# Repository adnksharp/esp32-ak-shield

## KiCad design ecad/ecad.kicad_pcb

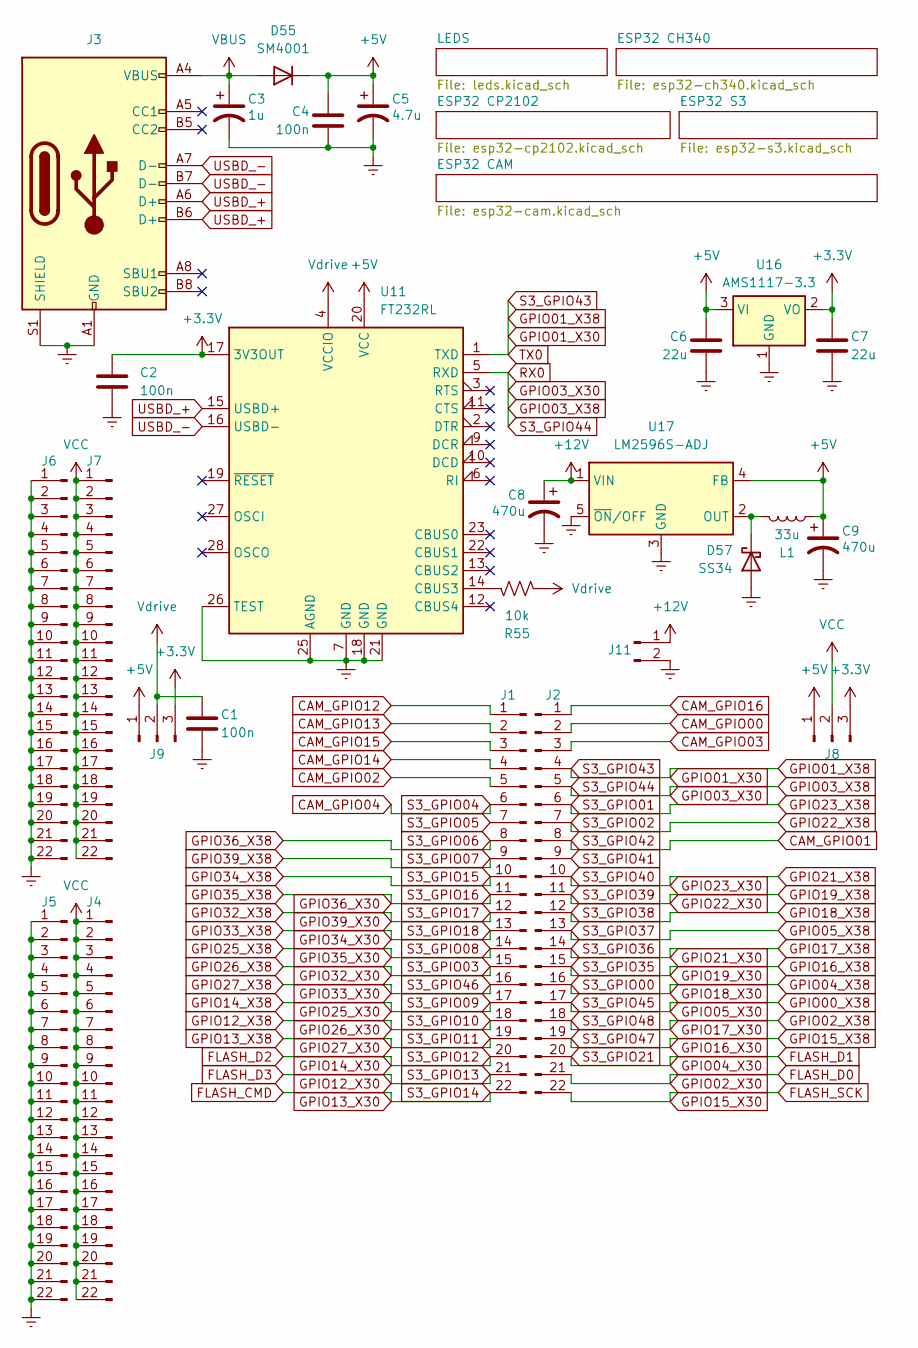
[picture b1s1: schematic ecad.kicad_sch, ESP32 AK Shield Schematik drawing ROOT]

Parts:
C1, C2, C4: 100n; C_0805_2012Metric_Pad1.18x1.45mm_HandSolder
C3: 1u; CP_Elec_4x5.4
C5: 4.7u; CP_Elec_4x5.4
C6, C7: 22u; C_0805_2012Metric_Pad1.18x1.45mm_HandSolder
C8, C9: 470u; CP_Elec_8x10.5
D55: SM4001; D_MELF
D57: SS34; D_SMA
J1, J2, J4, J5, J6, J7: Conn_01x22_Pin; PinHeader_1x22_P2.54mm_Vertical
J3: USB_C; USB_C_Receptacle_Palconn_UTC16-G
J8, J9: Conn_01x03_Pin; PinHeader_1x03_P2.54mm_Vertical
J11: Conn_01x02_Pin; BarrelJack_GCT_DCJ200-10-A_Horizontal
L1: 33u; L_6.3x6.3_H3
R55: 10k; R_0805_2012Metric_Pad1.20x1.40mm_HandSolder
U11: FT232RL; SSOP-28_5.3x10.2mm_P0.65mm
U16: AMS1117-3.3; SOT-223-3_TabPin2
U17: LM2596S-ADJ; TO-263-5_TabPin3

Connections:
+3.3V: C2.1, C7.1, J8.3, J9.3, U11.17 (3V3OUT), U16.2 (VO); also elsewhere on the board
+5V: C4.1, C5.1, C6.1, C9.1, D55.1 (K), J8.1, J9.1, L1.2, U11.20 (VCC), U16.3 (VI), U17.4 (FB); also elsewhere on the board
+12V: C8.1, J11.1, U17.1 (VIN); also elsewhere on the board
CAM_GPIO00: J2.2; also elsewhere on the board
CAM_GPIO01: J2.8; also elsewhere on the board
CAM_GPIO02: J1.5; also elsewhere on the board
CAM_GPIO03: J2.3; also elsewhere on the board
CAM_GPIO04: J1.6; also elsewhere on the board
CAM_GPIO12: J1.1; also elsewhere on the board
CAM_GPIO13: J1.2; also elsewhere on the board
CAM_GPIO14: J1.4; also elsewhere on the board
CAM_GPIO15: J1.3; also elsewhere on the board
CAM_GPIO16: J2.1; also elsewhere on the board
Earth: C1.2, C2.2, C3.2, C4.2, C5.2, C6.2, C7.2, C8.2, C9.2, D57.2 (A), J3.A1 (GND), J3.A12 (GND), J3.B1 (GND), J3.B12 (GND), J3.S1 (SHIELD), J5.1, J5.2, J5.3, J5.4, J5.5, J5.6, J5.7, J5.8, J5.9, J5.10, J5.11, J5.12, J5.13, J5.14, J5.15, J5.16, J5.17, J5.18, J5.19, J5.20, J5.21, J5.22, J6.1, J6.2, J6.3, J6.4, J6.5, J6.6, J6.7, J6.8, J6.9, J6.10, J6.11, J6.12, J6.13, J6.14, J6.15, J6.16, J6.17, J6.18, J6.19, J6.20, J6.21, J6.22, J11.2, U11.7 (GND), U11.18 (GND), U11.21 (GND), U11.25 (AGND), U11.26 (TEST), U16.1 (GND), U17.3 (GND), U17.5 (~ON/OFF); also elsewhere on the board
FLASH_CMD: J1.22; also elsewhere on the board
FLASH_D0: J2.21; also elsewhere on the board
FLASH_D1: J2.20; also elsewhere on the board
FLASH_D2: J1.20; also elsewhere on the board
FLASH_D3: J1.21; also elsewhere on the board
FLASH_SCK: J2.22; also elsewhere on the board
GPIO00_X38: J2.17; also elsewhere on the board
GPIO01_X30: J2.4, U11.1 (TXD); also elsewhere on the board
GPIO02_X38: J2.18; also elsewhere on the board
GPIO03_X30: J2.5, U11.5 (RXD); also elsewhere on the board
GPIO04_X38: J2.16; also elsewhere on the board
GPIO05_X38: J2.13; also elsewhere on the board
GPIO12_X38: J1.18; also elsewhere on the board
GPIO13_X38: J1.19; also elsewhere on the board
GPIO14_X38: J1.17; also elsewhere on the board
GPIO15_X38: J2.19; also elsewhere on the board
GPIO16_X38: J2.15; also elsewhere on the board
GPIO17_X38: J2.14; also elsewhere on the board
GPIO18_X38: J2.12; also elsewhere on the board
GPIO19_X38: J2.11; also elsewhere on the board
GPIO21_X38: J2.10; also elsewhere on the board
GPIO22_X38: J2.7; also elsewhere on the board
GPIO23_X38: J2.6; also elsewhere on the board
GPIO25_X38: J1.14; also elsewhere on the board
GPIO26_X38: J1.15; also elsewhere on the board
GPIO27_X38: J1.16; also elsewhere on the board
GPIO32_X38: J1.12; also elsewhere on the board
GPIO33_X38: J1.13; also elsewhere on the board
GPIO34_X38: J1.10; also elsewhere on the board
GPIO35_X38: J1.11; also elsewhere on the board
GPIO36_X38: J1.8; also elsewhere on the board
GPIO39_X38: J1.9; also elsewhere on the board
unnamed: D57.1 (K), L1.1, U17.2 (OUT)
unnamed: R55.1, U11.14 (CBUS3)
S3_GPIO05: J1.7; also elsewhere on the board
S3_GPIO41: J2.9; also elsewhere on the board
USBD_+: J3.A6 (D+), J3.B6 (D+), U11.15 (USBD+)
USBD_-: J3.A7 (D-), J3.B7 (D-), U11.16 (USBD-)
VBUS: C3.1, D55.2 (A), J3.A4 (VBUS), J3.A9 (VBUS), J3.B4 (VBUS), J3.B9 (VBUS); also elsewhere on the board
VCC: J4.1, J4.2, J4.3, J4.4, J4.5, J4.6, J4.7, J4.8, J4.9, J4.10, J4.11, J4.12, J4.13, J4.14, J4.15, J4.16, J4.17, J4.18, J4.19, J4.20, J4.21, J4.22, J7.1, J7.2, J7.3, J7.4, J7.5, J7.6, J7.7, J7.8, J7.9, J7.10, J7.11, J7.12, J7.13, J7.14, J7.15, J7.16, J7.17, J7.18, J7.19, J7.20, J7.21, J7.22, J8.2
Vdrive: C1.1, J9.2, R55.2, U11.4 (VCCIO)

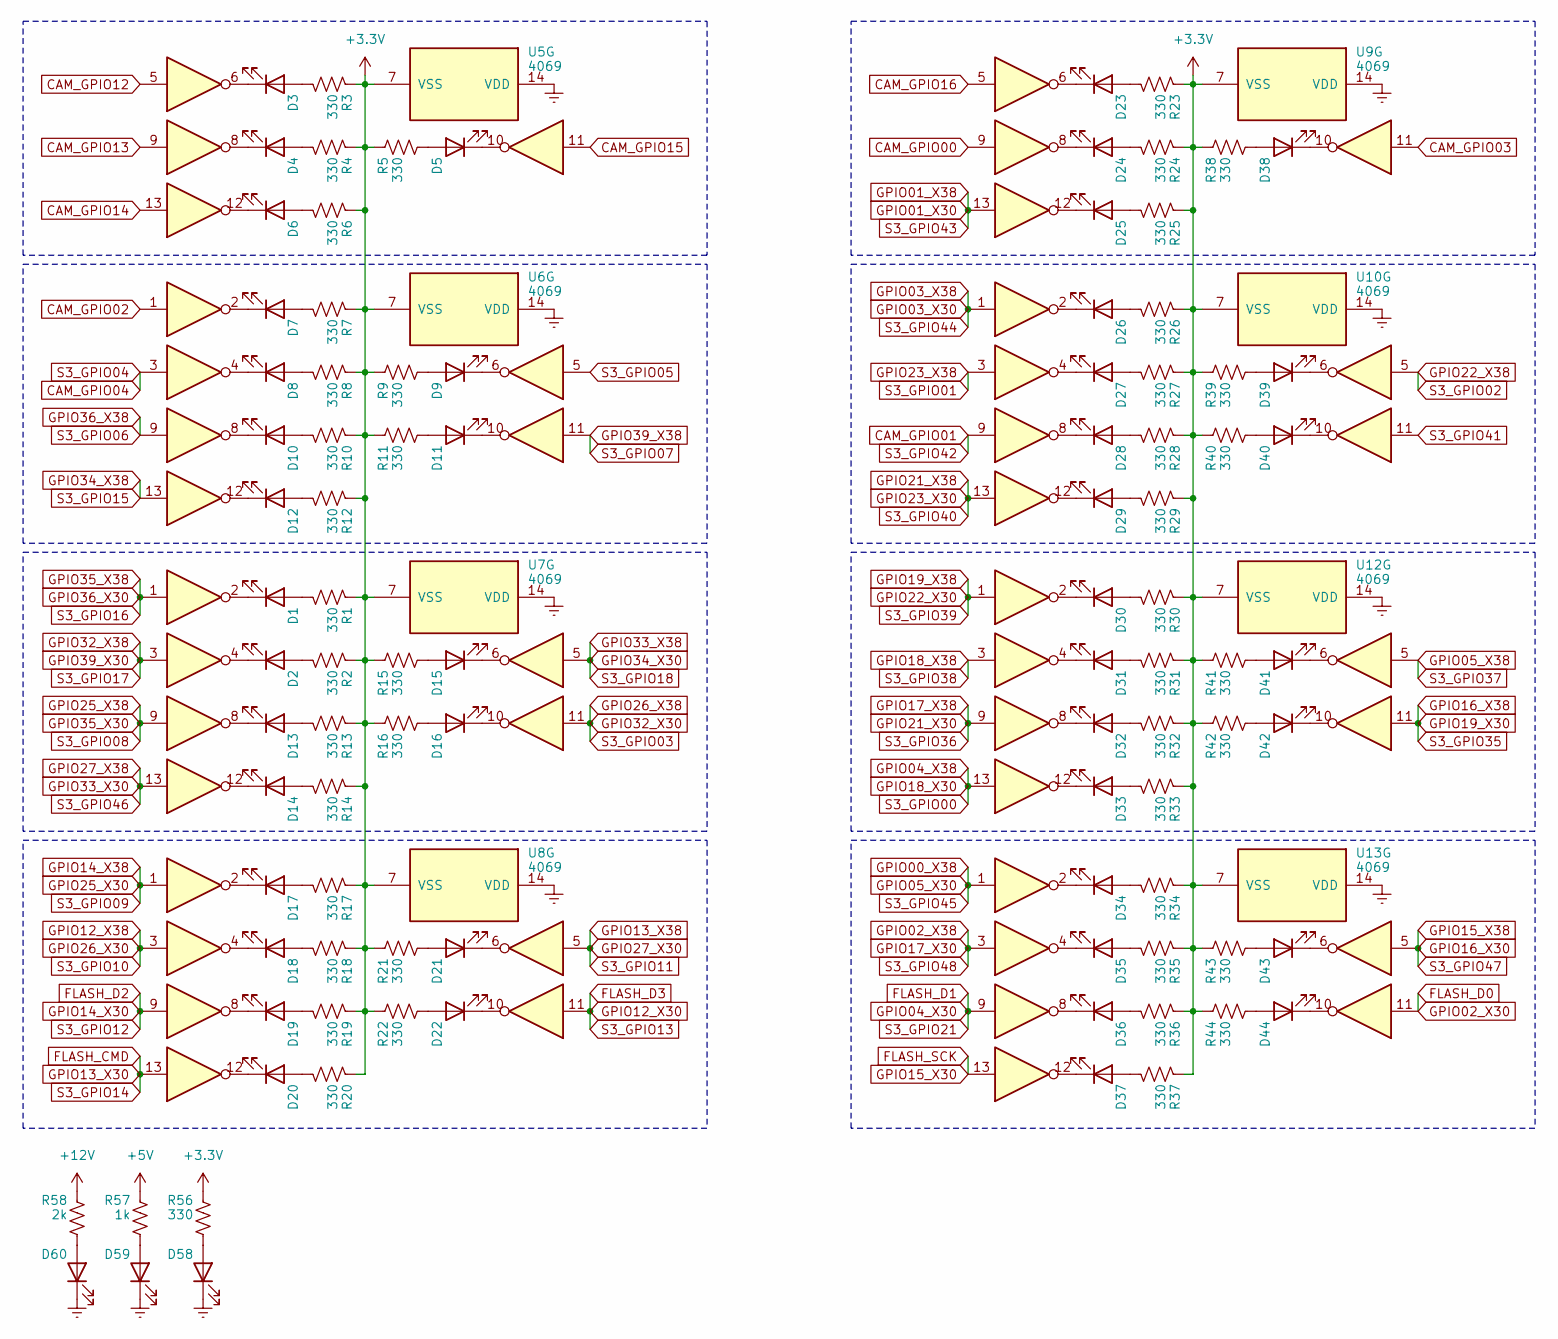
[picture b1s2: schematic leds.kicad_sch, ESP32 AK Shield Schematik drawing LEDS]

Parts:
D1, D2, D3, D4, D5, D6, D7, D8, D9, D10, D11, D12, D13, D14, D15, D16, D17, D18, D19, D20, D21, D22, D23, D24, D25, D26, D27, D28, D29, D30, D31, D32, D33, D34, D35, D36, D37, D38, D39, D40, D41, D42, D43, D44, D58, D59, D60: LED; LED_0805_2012Metric_Pad1.15x1.40mm_HandSolder
R1, R2, R3, R4, R5, R6, R7, R8, R9, R10, R11, R12, R13, R14, R15, R16, R17, R18, R19, R20, R21, R22, R23, R24, R25, R26, R27, R28, R29, R30, R31, R32, R33, R34, R35, R36, R37, R38, R39, R40, R41, R42, R43, R44, R56: 330; R_0805_2012Metric_Pad1.20x1.40mm_HandSolder
R57: 1k; R_0805_2012Metric_Pad1.20x1.40mm_HandSolder
R58: 2k; R_0805_2012Metric_Pad1.20x1.40mm_HandSolder
U5, U6, U7, U8, U9, U10, U12, U13: 4069; DIP-14_W8.89mm_SMDSocket_LongPads

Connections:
+3.3V: R1.2, R2.2, R3.2, R4.2, R5.2, R6.2, R7.2, R8.2, R9.2, R10.2, R11.2, R12.2, R13.2, R14.2, R15.2, R16.2, R17.2, R18.2, R19.2, R20.2, R21.2, R22.2, R23.2, R24.2, R25.2, R26.2, R27.2, R28.2, R29.2, R30.2, R31.2, R32.2, R33.2, R34.2, R35.2, R36.2, R37.2, R38.2, R39.2, R40.2, R41.2, R42.2, R43.2, R44.2, R56.2, U5.7 (VSS), U6.7 (VSS), U7.7 (VSS), U8.7 (VSS), U9.7 (VSS), U10.7 (VSS), U12.7 (VSS), U13.7 (VSS); also elsewhere on the board
+5V: R57.2; also elsewhere on the board
+12V: R58.2; also elsewhere on the board
CAM_GPIO00: U9.9; also elsewhere on the board
CAM_GPIO01: U10.9; also elsewhere on the board
CAM_GPIO02: U6.1; also elsewhere on the board
CAM_GPIO03: U9.11; also elsewhere on the board
CAM_GPIO04: U6.3; also elsewhere on the board
CAM_GPIO12: U5.5; also elsewhere on the board
CAM_GPIO13: U5.9; also elsewhere on the board
CAM_GPIO14: U5.13; also elsewhere on the board
CAM_GPIO15: U5.11; also elsewhere on the board
CAM_GPIO16: U9.5; also elsewhere on the board
Earth: D58.1 (K), D59.1 (K), D60.1 (K), U5.14 (VDD), U6.14 (VDD), U7.14 (VDD), U8.14 (VDD), U9.14 (VDD), U10.14 (VDD), U12.14 (VDD), U13.14 (VDD); also elsewhere on the board
FLASH_CMD: U8.13; also elsewhere on the board
FLASH_D0: U13.11; also elsewhere on the board
FLASH_D1: U13.9; also elsewhere on the board
FLASH_D2: U8.9; also elsewhere on the board
FLASH_D3: U8.11; also elsewhere on the board
FLASH_SCK: U13.13; also elsewhere on the board
GPIO00_X38: U13.1; also elsewhere on the board
GPIO01_X30: U9.13; also elsewhere on the board
GPIO02_X38: U13.3; also elsewhere on the board
GPIO03_X30: U10.1; also elsewhere on the board
GPIO04_X38: U12.13; also elsewhere on the board
GPIO05_X38: U12.5; also elsewhere on the board
GPIO12_X38: U8.3; also elsewhere on the board
GPIO13_X38: U8.5; also elsewhere on the board
GPIO14_X38: U8.1; also elsewhere on the board
GPIO15_X38: U13.5; also elsewhere on the board
GPIO16_X38: U12.11; also elsewhere on the board
GPIO17_X38: U12.9; also elsewhere on the board
GPIO18_X38: U12.3; also elsewhere on the board
GPIO19_X38: U12.1; also elsewhere on the board
GPIO21_X38: U10.13; also elsewhere on the board
GPIO22_X38: U10.5; also elsewhere on the board
GPIO23_X38: U10.3; also elsewhere on the board
GPIO25_X38: U7.9; also elsewhere on the board
GPIO26_X38: U7.11; also elsewhere on the board
GPIO27_X38: U7.13; also elsewhere on the board
GPIO32_X38: U7.3; also elsewhere on the board
GPIO33_X38: U7.5; also elsewhere on the board
GPIO34_X38: U6.13; also elsewhere on the board
GPIO35_X38: U7.1; also elsewhere on the board
GPIO36_X38: U6.9; also elsewhere on the board
GPIO39_X38: U6.11; also elsewhere on the board
unnamed: D1.2 (A), R1.1
unnamed: D1.1 (K), U7.2
unnamed: D2.2 (A), R2.1
unnamed: D2.1 (K), U7.4
unnamed: D3.2 (A), R3.1
unnamed: D3.1 (K), U5.6
unnamed: D4.2 (A), R4.1
unnamed: D4.1 (K), U5.8
unnamed: D5.2 (A), R5.1
unnamed: D5.1 (K), U5.10
unnamed: D6.2 (A), R6.1
unnamed: D6.1 (K), U5.12
unnamed: D7.2 (A), R7.1
unnamed: D7.1 (K), U6.2
unnamed: D8.2 (A), R8.1
unnamed: D8.1 (K), U6.4
unnamed: D9.2 (A), R9.1
unnamed: D9.1 (K), U6.6
unnamed: D10.2 (A), R10.1
unnamed: D10.1 (K), U6.8
unnamed: D11.2 (A), R11.1
unnamed: D11.1 (K), U6.10
unnamed: D12.2 (A), R12.1
unnamed: D12.1 (K), U6.12
unnamed: D13.2 (A), R13.1
unnamed: D13.1 (K), U7.8
unnamed: D14.2 (A), R14.1
unnamed: D14.1 (K), U7.12
unnamed: D15.2 (A), R15.1
unnamed: D15.1 (K), U7.6
unnamed: D16.2 (A), R16.1
unnamed: D16.1 (K), U7.10
unnamed: D17.2 (A), R17.1
unnamed: D17.1 (K), U8.2
unnamed: D18.2 (A), R18.1
unnamed: D18.1 (K), U8.4
unnamed: D19.2 (A), R19.1
unnamed: D19.1 (K), U8.8
unnamed: D20.2 (A), R20.1
unnamed: D20.1 (K), U8.12
unnamed: D21.2 (A), R21.1
unnamed: D21.1 (K), U8.6
unnamed: D22.2 (A), R22.1
unnamed: D22.1 (K), U8.10
unnamed: D23.2 (A), R23.1
unnamed: D23.1 (K), U9.6
unnamed: D24.2 (A), R24.1
unnamed: D24.1 (K), U9.8
unnamed: D25.2 (A), R25.1
unnamed: D25.1 (K), U9.12
unnamed: D26.2 (A), R26.1
unnamed: D26.1 (K), U10.2
unnamed: D27.2 (A), R27.1
unnamed: D27.1 (K), U10.4
unnamed: D28.2 (A), R28.1
unnamed: D28.1 (K), U10.8
unnamed: D29.2 (A), R29.1
unnamed: D29.1 (K), U10.12
unnamed: D30.2 (A), R30.1
unnamed: D30.1 (K), U12.2
unnamed: D31.2 (A), R31.1
unnamed: D31.1 (K), U12.4
unnamed: D32.2 (A), R32.1
unnamed: D32.1 (K), U12.8
unnamed: D33.2 (A), R33.1
unnamed: D33.1 (K), U12.12
unnamed: D34.2 (A), R34.1
unnamed: D34.1 (K), U13.2
unnamed: D35.2 (A), R35.1
unnamed: D35.1 (K), U13.4
unnamed: D36.2 (A), R36.1
unnamed: D36.1 (K), U13.8
unnamed: D37.2 (A), R37.1
unnamed: D37.1 (K), U13.12
unnamed: D38.2 (A), R38.1
unnamed: D38.1 (K), U9.10
unnamed: D39.2 (A), R39.1
unnamed: D39.1 (K), U10.6
unnamed: D40.2 (A), R40.1
unnamed: D40.1 (K), U10.10
unnamed: D41.2 (A), R41.1
unnamed: D41.1 (K), U12.6
unnamed: D42.2 (A), R42.1
unnamed: D42.1 (K), U12.10
unnamed: D43.2 (A), R43.1
unnamed: D43.1 (K), U13.6
unnamed: D44.2 (A), R44.1
unnamed: D44.1 (K), U13.10
unnamed: D58.2 (A), R56.1
unnamed: D59.2 (A), R57.1
unnamed: D60.2 (A), R58.1
S3_GPIO05: U6.5; also elsewhere on the board
S3_GPIO41: U10.11; also elsewhere on the board

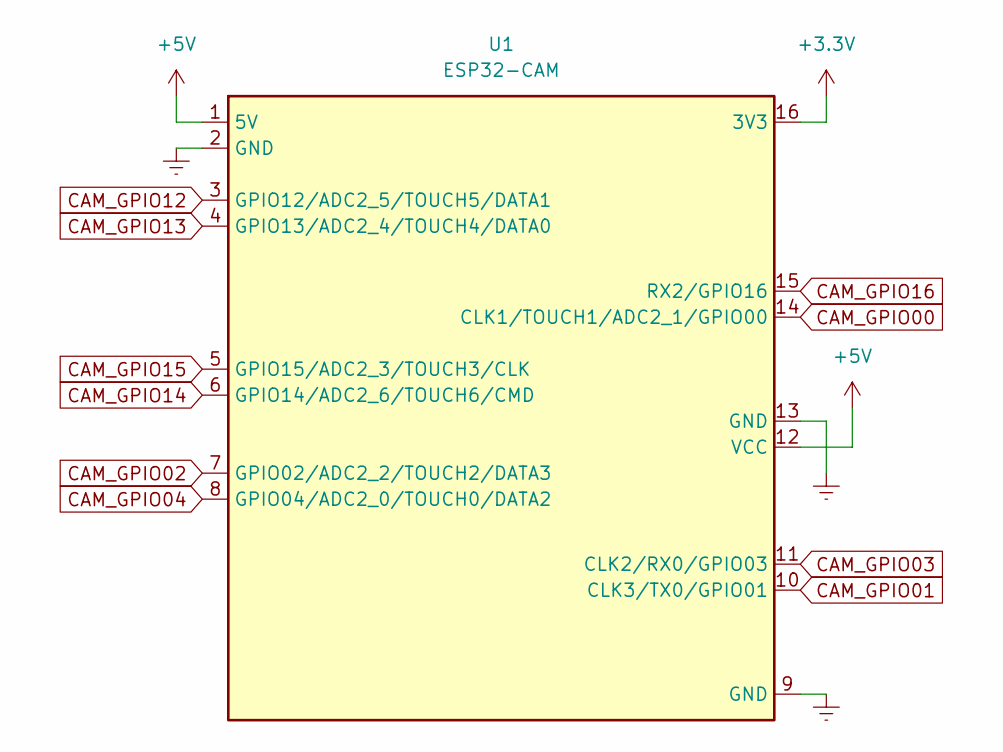
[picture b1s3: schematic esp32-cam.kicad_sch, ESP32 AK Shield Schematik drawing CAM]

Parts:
U1: ESP32-CAM; ESP32-CAM-DEVKIT

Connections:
+3.3V: U1.16 (3V3); also elsewhere on the board
+5V: U1.1 (5V), U1.12 (VCC); also elsewhere on the board
CAM_GPIO00: U1.14 (CLK1/TOUCH1/ADC2_1/GPIO00); also elsewhere on the board
CAM_GPIO01: U1.10 (CLK3/TX0/GPIO01); also elsewhere on the board
CAM_GPIO02: U1.7 (GPIO02/ADC2_2/TOUCH2/DATA3); also elsewhere on the board
CAM_GPIO03: U1.11 (CLK2/RX0/GPIO03); also elsewhere on the board
CAM_GPIO04: U1.8 (GPIO04/ADC2_0/TOUCH0/DATA2); also elsewhere on the board
CAM_GPIO12: U1.3 (GPIO12/ADC2_5/TOUCH5/DATA1); also elsewhere on the board
CAM_GPIO13: U1.4 (GPIO13/ADC2_4/TOUCH4/DATA0); also elsewhere on the board
CAM_GPIO14: U1.6 (GPIO14/ADC2_6/TOUCH6/CMD); also elsewhere on the board
CAM_GPIO15: U1.5 (GPIO15/ADC2_3/TOUCH3/CLK); also elsewhere on the board
CAM_GPIO16: U1.15 (RX2/GPIO16); also elsewhere on the board
Earth: U1.2 (GND), U1.9 (GND), U1.13 (GND); also elsewhere on the board

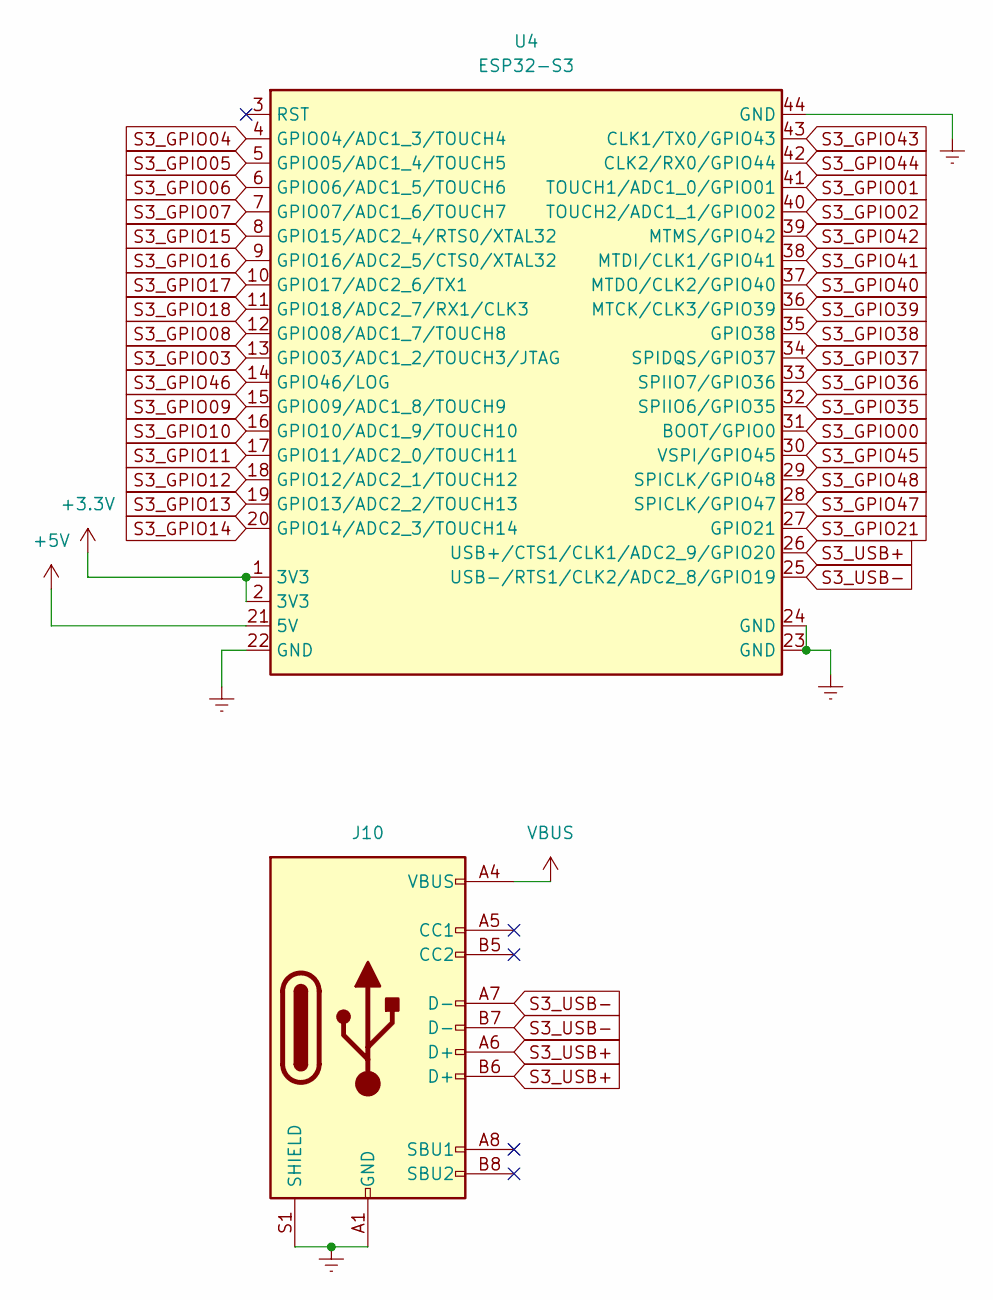
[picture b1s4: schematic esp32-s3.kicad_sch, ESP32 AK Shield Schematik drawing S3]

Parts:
J10: USB_C; USB_C_Receptacle_Palconn_UTC16-G
U4: ESP32-S3; ESP32-S3-DEVKIT_CH343p

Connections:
+3.3V: U4.1 (3V3), U4.2 (3V3); also elsewhere on the board
+5V: U4.21 (5V); also elsewhere on the board
CAM_GPIO01: U4.39 (MTMS/GPIO42); also elsewhere on the board
CAM_GPIO04: U4.4 (GPIO04/ADC1_3/TOUCH4); also elsewhere on the board
Earth: J10.A1 (GND), J10.A12 (GND), J10.B1 (GND), J10.B12 (GND), J10.S1 (SHIELD), U4.22 (GND), U4.23 (GND), U4.24 (GND), U4.44 (GND); also elsewhere on the board
FLASH_CMD: U4.20 (GPIO14/ADC2_3/TOUCH14); also elsewhere on the board
FLASH_D1: U4.27 (GPIO21); also elsewhere on the board
FLASH_D2: U4.18 (GPIO12/ADC2_1/TOUCH12); also elsewhere on the board
FLASH_D3: U4.19 (GPIO13/ADC2_2/TOUCH13); also elsewhere on the board
GPIO00_X38: U4.30 (VSPI/GPIO45); also elsewhere on the board
GPIO01_X30: U4.43 (CLK1/TX0/GPIO43); also elsewhere on the board
GPIO02_X38: U4.29 (SPICLK/GPIO48); also elsewhere on the board
GPIO03_X30: U4.42 (CLK2/RX0/GPIO44); also elsewhere on the board
GPIO04_X38: U4.31 (BOOT/GPIO0); also elsewhere on the board
GPIO05_X38: U4.34 (SPIDQS/GPIO37); also elsewhere on the board
GPIO12_X38: U4.16 (GPIO10/ADC1_9/TOUCH10); also elsewhere on the board
GPIO13_X38: U4.17 (GPIO11/ADC2_0/TOUCH11); also elsewhere on the board
GPIO14_X38: U4.15 (GPIO09/ADC1_8/TOUCH9); also elsewhere on the board
GPIO15_X38: U4.28 (SPICLK/GPIO47); also elsewhere on the board
GPIO16_X38: U4.32 (SPIIO6/GPIO35); also elsewhere on the board
GPIO17_X38: U4.33 (SPIIO7/GPIO36); also elsewhere on the board
GPIO18_X38: U4.35 (GPIO38); also elsewhere on the board
GPIO19_X38: U4.36 (MTCK/CLK3/GPIO39); also elsewhere on the board
GPIO21_X38: U4.37 (MTDO/CLK2/GPIO40); also elsewhere on the board
GPIO22_X38: U4.40 (TOUCH2/ADC1_1/GPIO02); also elsewhere on the board
GPIO23_X38: U4.41 (TOUCH1/ADC1_0/GPIO01); also elsewhere on the board
GPIO25_X38: U4.12 (GPIO08/ADC1_7/TOUCH8); also elsewhere on the board
GPIO26_X38: U4.13 (GPIO03/ADC1_2/TOUCH3/JTAG); also elsewhere on the board
GPIO27_X38: U4.14 (GPIO46/LOG); also elsewhere on the board
GPIO32_X38: U4.10 (GPIO17/ADC2_6/TX1); also elsewhere on the board
GPIO33_X38: U4.11 (GPIO18/ADC2_7/RX1/CLK3); also elsewhere on the board
GPIO34_X38: U4.8 (GPIO15/ADC2_4/RTS0/XTAL32); also elsewhere on the board
GPIO35_X38: U4.9 (GPIO16/ADC2_5/CTS0/XTAL32); also elsewhere on the board
GPIO36_X38: U4.6 (GPIO06/ADC1_5/TOUCH6); also elsewhere on the board
GPIO39_X38: U4.7 (GPIO07/ADC1_6/TOUCH7); also elsewhere on the board
S3_GPIO05: U4.5 (GPIO05/ADC1_4/TOUCH5); also elsewhere on the board
S3_GPIO41: U4.38 (MTDI/CLK1/GPIO41); also elsewhere on the board
S3_USB+: J10.A6 (D+), J10.B6 (D+), U4.26 (USB+/CTS1/CLK1/ADC2_9/GPIO20)
S3_USB-: J10.A7 (D-), J10.B7 (D-), U4.25 (USB-/RTS1/CLK2/ADC2_8/GPIO19)
VBUS: J10.A4 (VBUS), J10.A9 (VBUS), J10.B4 (VBUS), J10.B9 (VBUS); also elsewhere on the board

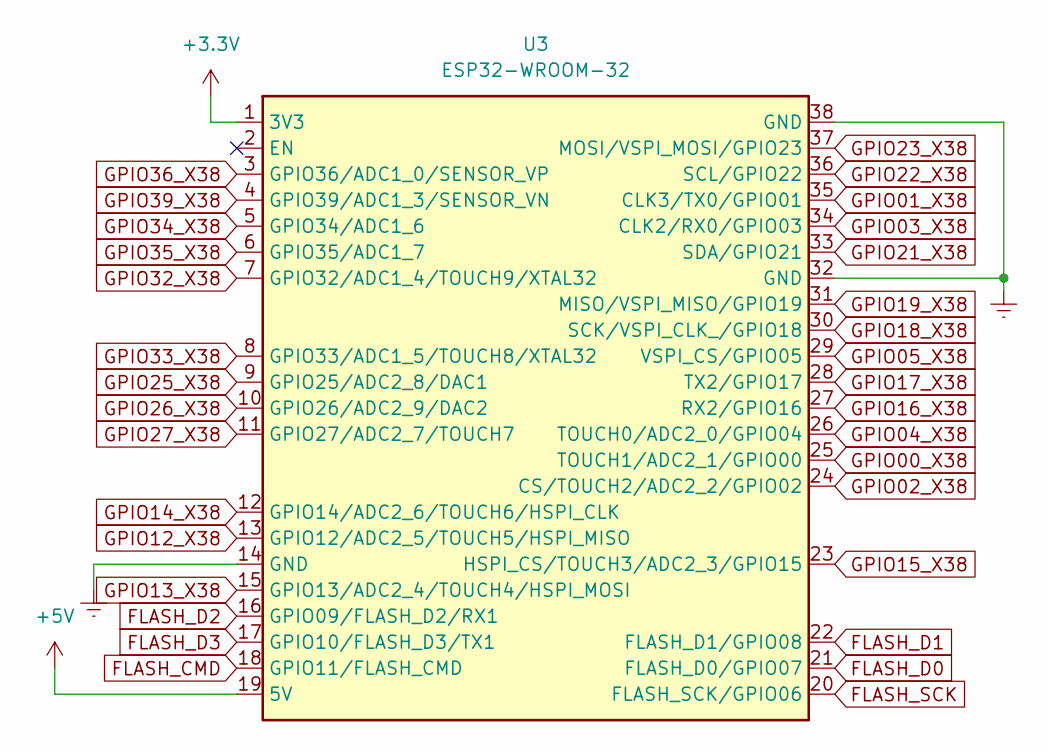
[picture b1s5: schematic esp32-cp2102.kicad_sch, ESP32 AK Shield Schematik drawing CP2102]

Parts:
U3: ESP32-WROOM-32; ESP32-DEVKIT_CP2102

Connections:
+3.3V: U3.1 (3V3); also elsewhere on the board
+5V: U3.19 (5V); also elsewhere on the board
Earth: U3.14 (GND), U3.32 (GND), U3.38 (GND); also elsewhere on the board
FLASH_CMD: U3.18 (GPIO11/FLASH_CMD); also elsewhere on the board
FLASH_D0: U3.21 (FLASH_D0/GPIO07); also elsewhere on the board
FLASH_D1: U3.22 (FLASH_D1/GPIO08); also elsewhere on the board
FLASH_D2: U3.16 (GPIO09/FLASH_D2/RX1); also elsewhere on the board
FLASH_D3: U3.17 (GPIO10/FLASH_D3/TX1); also elsewhere on the board
FLASH_SCK: U3.20 (FLASH_SCK/GPIO06); also elsewhere on the board
GPIO00_X38: U3.25 (TOUCH1/ADC2_1/GPIO00); also elsewhere on the board
GPIO01_X30: U3.35 (CLK3/TX0/GPIO01); also elsewhere on the board
GPIO02_X38: U3.24 (CS/TOUCH2/ADC2_2/GPIO02); also elsewhere on the board
GPIO03_X30: U3.34 (CLK2/RX0/GPIO03); also elsewhere on the board
GPIO04_X38: U3.26 (TOUCH0/ADC2_0/GPIO04); also elsewhere on the board
GPIO05_X38: U3.29 (VSPI_CS/GPIO05); also elsewhere on the board
GPIO12_X38: U3.13 (GPIO12/ADC2_5/TOUCH5/HSPI_MISO); also elsewhere on the board
GPIO13_X38: U3.15 (GPIO13/ADC2_4/TOUCH4/HSPI_MOSI); also elsewhere on the board
GPIO14_X38: U3.12 (GPIO14/ADC2_6/TOUCH6/HSPI_CLK); also elsewhere on the board
GPIO15_X38: U3.23 (HSPI_CS/TOUCH3/ADC2_3/GPIO15); also elsewhere on the board
GPIO16_X38: U3.27 (RX2/GPIO16); also elsewhere on the board
GPIO17_X38: U3.28 (TX2/GPIO17); also elsewhere on the board
GPIO18_X38: U3.30 (SCK/VSPI_CLK_/GPIO18); also elsewhere on the board
GPIO19_X38: U3.31 (MISO/VSPI_MISO/GPIO19); also elsewhere on the board
GPIO21_X38: U3.33 (SDA/GPIO21); also elsewhere on the board
GPIO22_X38: U3.36 (SCL/GPIO22); also elsewhere on the board
GPIO23_X38: U3.37 (MOSI/VSPI_MOSI/GPIO23); also elsewhere on the board
GPIO25_X38: U3.9 (GPIO25/ADC2_8/DAC1); also elsewhere on the board
GPIO26_X38: U3.10 (GPIO26/ADC2_9/DAC2); also elsewhere on the board
GPIO27_X38: U3.11 (GPIO27/ADC2_7/TOUCH7); also elsewhere on the board
GPIO32_X38: U3.7 (GPIO32/ADC1_4/TOUCH9/XTAL32); also elsewhere on the board
GPIO33_X38: U3.8 (GPIO33/ADC1_5/TOUCH8/XTAL32); also elsewhere on the board
GPIO34_X38: U3.5 (GPIO34/ADC1_6); also elsewhere on the board
GPIO35_X38: U3.6 (GPIO35/ADC1_7); also elsewhere on the board
GPIO36_X38: U3.3 (GPIO36/ADC1_0/SENSOR_VP); also elsewhere on the board
GPIO39_X38: U3.4 (GPIO39/ADC1_3/SENSOR_VN); also elsewhere on the board

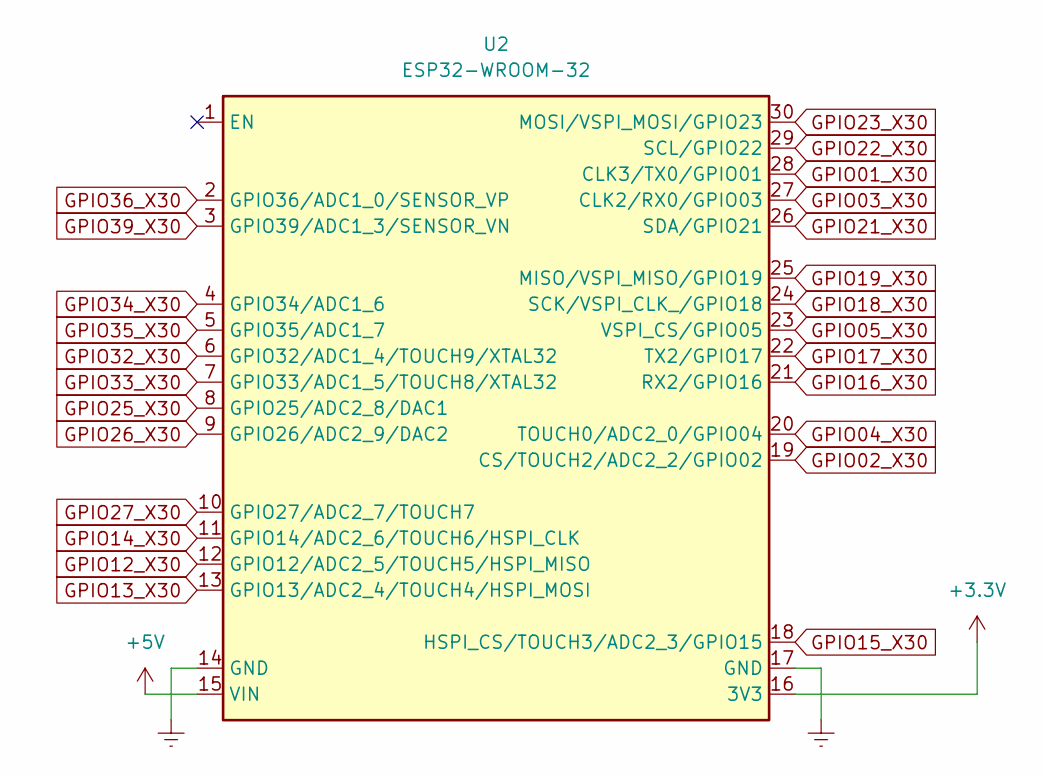
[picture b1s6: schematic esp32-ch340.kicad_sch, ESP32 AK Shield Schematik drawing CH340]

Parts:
U2: ESP32-WROOM-32; ESP32-DEVKIT_CH340C

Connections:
+3.3V: U2.16 (3V3); also elsewhere on the board
+5V: U2.15 (VIN); also elsewhere on the board
Earth: U2.14 (GND), U2.17 (GND); also elsewhere on the board
FLASH_CMD: U2.13 (GPIO13/ADC2_4/TOUCH4/HSPI_MOSI); also elsewhere on the board
FLASH_D0: U2.19 (CS/TOUCH2/ADC2_2/GPIO02); also elsewhere on the board
FLASH_D1: U2.20 (TOUCH0/ADC2_0/GPIO04); also elsewhere on the board
FLASH_D2: U2.11 (GPIO14/ADC2_6/TOUCH6/HSPI_CLK); also elsewhere on the board
FLASH_D3: U2.12 (GPIO12/ADC2_5/TOUCH5/HSPI_MISO); also elsewhere on the board
FLASH_SCK: U2.18 (HSPI_CS/TOUCH3/ADC2_3/GPIO15); also elsewhere on the board
GPIO00_X38: U2.23 (VSPI_CS/GPIO05); also elsewhere on the board
GPIO01_X30: U2.28 (CLK3/TX0/GPIO01); also elsewhere on the board
GPIO02_X38: U2.22 (TX2/GPIO17); also elsewhere on the board
GPIO03_X30: U2.27 (CLK2/RX0/GPIO03); also elsewhere on the board
GPIO04_X38: U2.24 (SCK/VSPI_CLK_/GPIO18); also elsewhere on the board
GPIO12_X38: U2.9 (GPIO26/ADC2_9/DAC2); also elsewhere on the board
GPIO13_X38: U2.10 (GPIO27/ADC2_7/TOUCH7); also elsewhere on the board
GPIO14_X38: U2.8 (GPIO25/ADC2_8/DAC1); also elsewhere on the board
GPIO15_X38: U2.21 (RX2/GPIO16); also elsewhere on the board
GPIO16_X38: U2.25 (MISO/VSPI_MISO/GPIO19); also elsewhere on the board
GPIO17_X38: U2.26 (SDA/GPIO21); also elsewhere on the board
GPIO19_X38: U2.29 (SCL/GPIO22); also elsewhere on the board
GPIO21_X38: U2.30 (MOSI/VSPI_MOSI/GPIO23); also elsewhere on the board
GPIO25_X38: U2.5 (GPIO35/ADC1_7); also elsewhere on the board
GPIO26_X38: U2.6 (GPIO32/ADC1_4/TOUCH9/XTAL32); also elsewhere on the board
GPIO27_X38: U2.7 (GPIO33/ADC1_5/TOUCH8/XTAL32); also elsewhere on the board
GPIO32_X38: U2.3 (GPIO39/ADC1_3/SENSOR_VN); also elsewhere on the board
GPIO33_X38: U2.4 (GPIO34/ADC1_6); also elsewhere on the board
GPIO35_X38: U2.2 (GPIO36/ADC1_0/SENSOR_VP); also elsewhere on the board

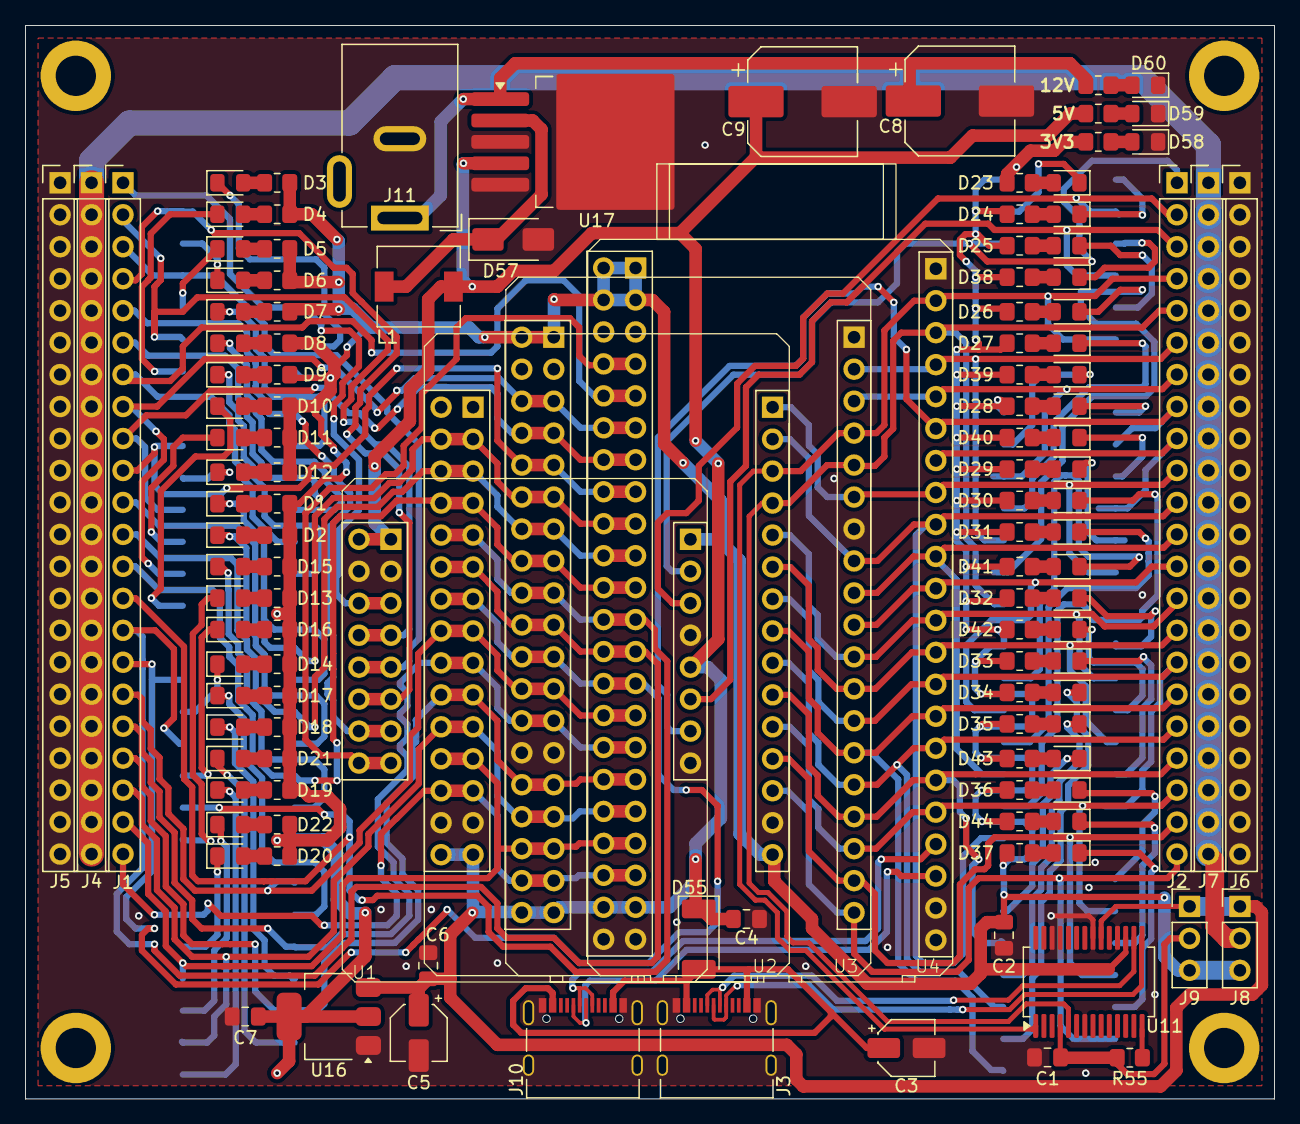
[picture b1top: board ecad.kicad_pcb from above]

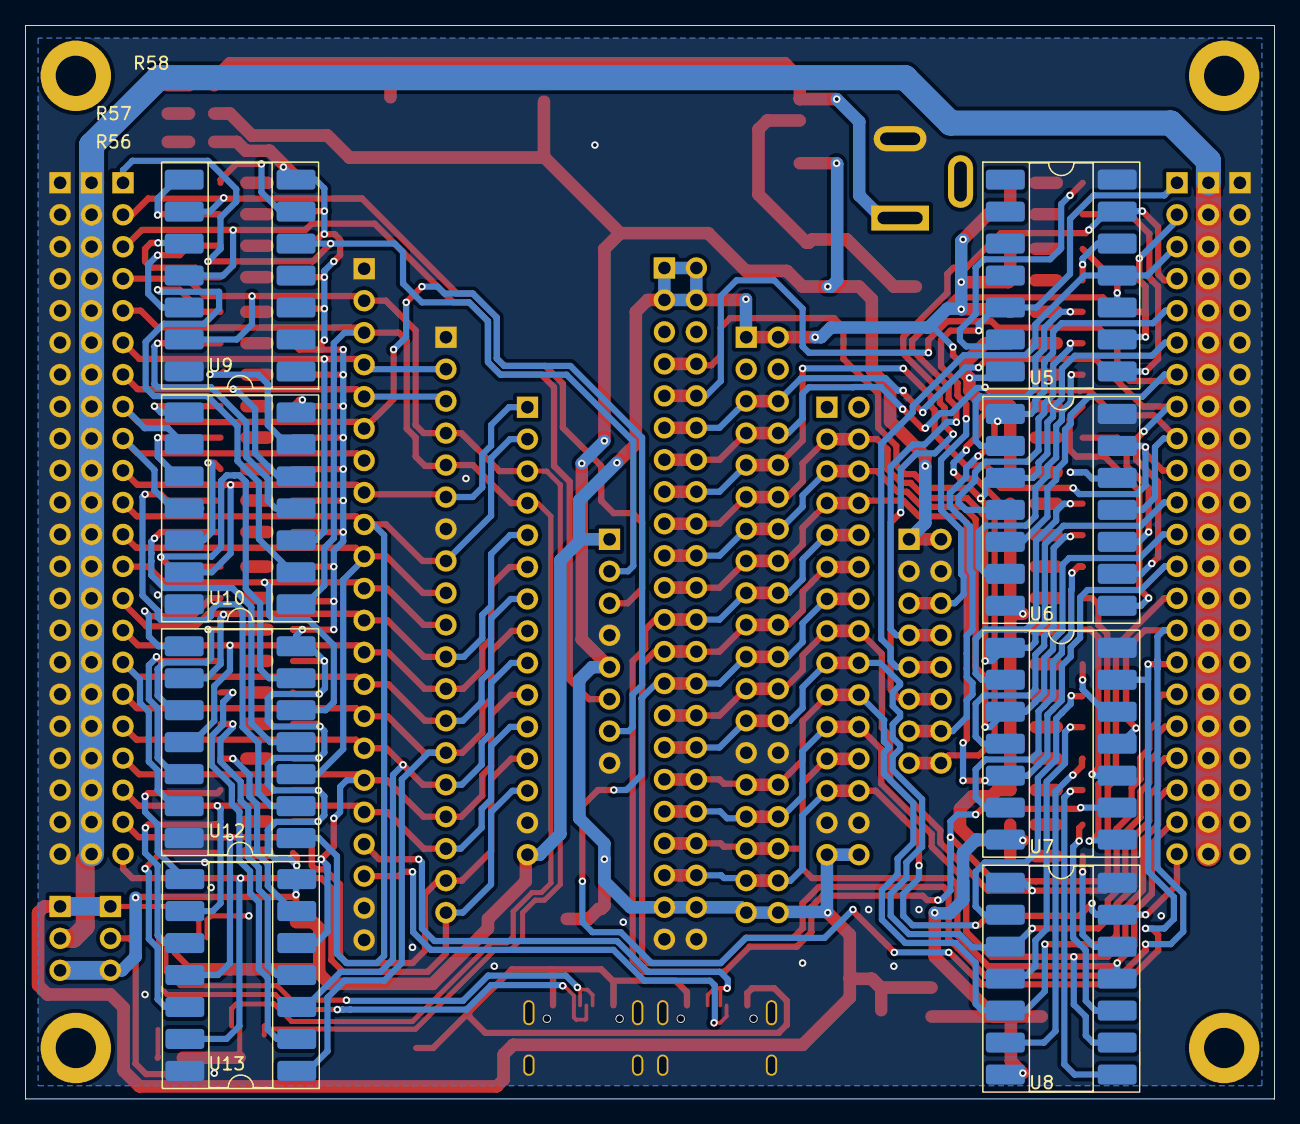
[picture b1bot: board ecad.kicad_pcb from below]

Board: 2 copper layers, 99.2 x 85.3 mm, 133 parts (8 on the bottom side), 148 nets.

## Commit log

2025-12-17 chore (ecad): init KiCad project
2025-12-18 feat (ecad): Add custom ESP32-CH340 devkit symbol
2025-12-19 feat (ecad): Add custom ESP32-CP2102 devkit symbol
2025-12-19 chore (ecad): exclude KiCad backups from repo
2025-12-19 feat (ecad): Add custom ESP32-CAM devkit symbol
2025-12-20 feat (ecad): Add custom ESP32-S3 devkit symbol
2025-12-20 chore (ecad): Config paper sizes
2025-12-20 chore (ecad): exclude temporal KiCad files
2025-12-21 chore (ecad): add board-step files
2025-12-21 feat (ecad): init ESP32 CH340 footprint
2025-12-21 feat (ecad): init ESP32-CP2102 footprint
2025-12-21 feat (ecad): init ESP32-S3 footprint
2025-12-22 refactor (ecad): edit ESP32-CH340 courtyard footprint
2025-12-22 refactor (ecad): edit ESP32-CH340 footprint pad enum
2025-12-22 refactor (ecad): update ESP32-CP2102 courtyard footprint
2025-12-22 refactor (ecad): edit ESP32-CP2102 footprint pad enum
2025-12-22 refactor (ecad): update ESP32-S3 courtyard footprint
2025-12-22 feat (ecad): init ESP32-CAM footprint
2025-12-22 refactor (ecad): edit ESP32-CAM footprint pad enum
2025-12-22 refactor (ecad): edit ESP32-CP2102 symbol pad enum
2025-12-22 feat (ecad): link footprints to symbols
2025-12-22 chore (ecad): init PCB & Schematic
2025-12-24 fead (ecad): update ESP32-CAM Schematic
2025-12-24 fead (ecad): update ESP32-CH340 Schematic
2025-12-24 fead (ecad): update ESP32-CP2102 Schematic
2025-12-24 fead (ecad): update ESP32-S3 Schematic
2025-12-24 feat (ecad): add LEDs Schematic
2025-12-24 feat (ecad): update KiCad project
2025-12-26 feat (ecad): start PCB design
    Left header pins and LEDs connected to devkits without ground-voltage
2025-12-31 feat (ecad): update PCB design
    header pins and LEDs connected to devkits without ground-voltage
2026-01-01 feat (ecad): update PCB design
    Connect power
2026-01-01 chore (ecad): update PCB design
